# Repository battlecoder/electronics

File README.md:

# electronics
Small Hardware projects that you will most likely find described in my blog: blog.damnsoft.org

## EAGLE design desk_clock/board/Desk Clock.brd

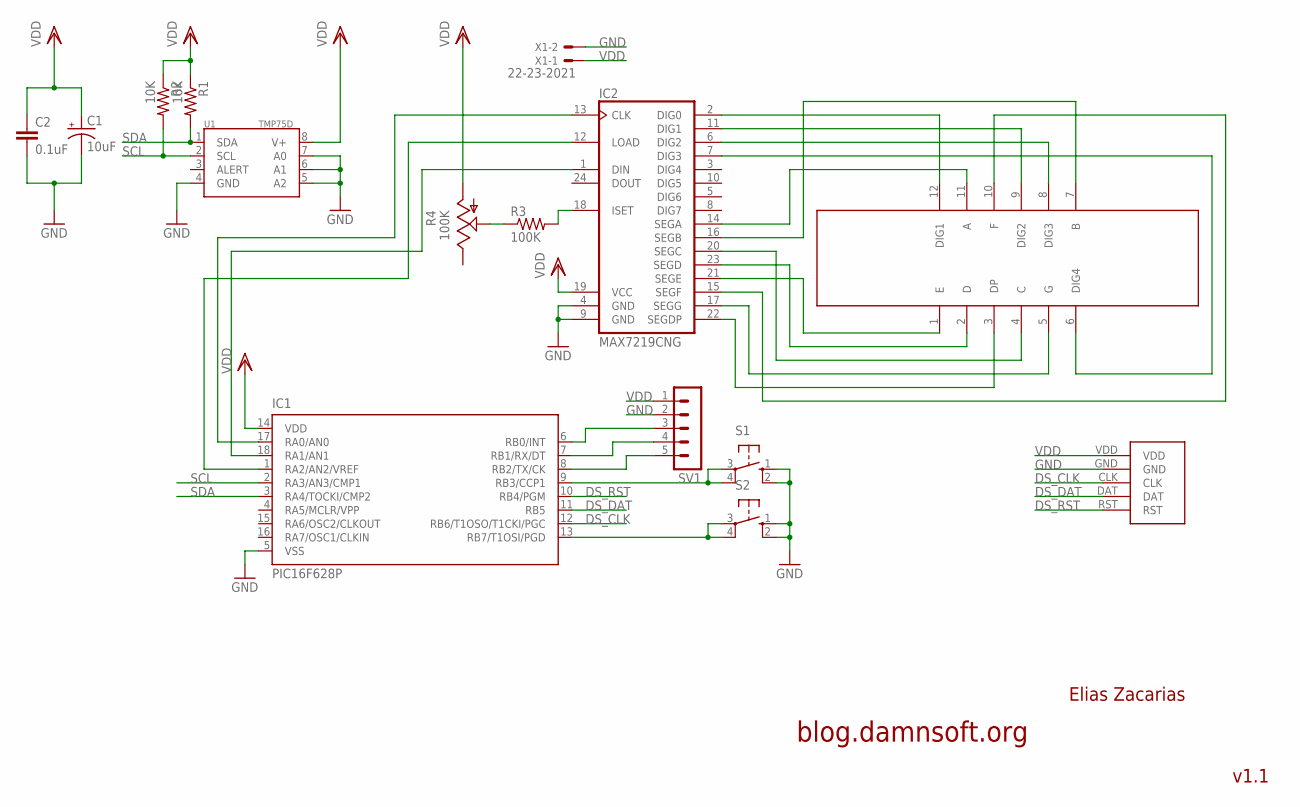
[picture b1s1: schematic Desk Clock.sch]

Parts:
C1: 10uF; E2-4
C2: 0.1uF; C025-025X050
IC1: PIC16F628P; DIL18
IC2: MAX7219CNG; DIL24-3
R1, R2: 10K; 0207/10
R3: 100K; 0207/10
R4: 100K; CA6V
S1, S2: 10-XX; B3F-10XX
SV1: MA05-1
U1: TMP75D; SO-08
U$1: NFD-5642BX; DISPLAY
U$2: DS1302_BOARD
X1: 22-23-2021

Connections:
DS_CLK: IC1.12 (RB6/T1OSO/T1CKI/PGC), U$2.CLK
DS_DAT: IC1.11 (RB5), U$2.DAT
DS_RST: IC1.10 (RB4/PGM), U$2.RST
GND: C1.-, C2.2, IC1.5 (VSS), IC2.4 (GND), IC2.9 (GND), S1.1 (S), S1.2 (S1), S2.1 (S), S2.2 (S1), SV1.2, U1.4 (GND), U1.5 (A2), U1.6 (A1), U1.7 (A0), U$2.GND, X1.2
unnamed: IC2.2 (DIG0), U$1.12 (DIG1)
unnamed: IC2.11 (DIG1), U$1.9 (DIG2)
unnamed: IC2.6 (DIG2), U$1.8 (DIG3)
unnamed: IC2.22 (SEGDP), U$1.3 (DP)
unnamed: IC2.17 (SEGG), U$1.5 (G)
unnamed: IC2.7 (DIG3), U$1.6 (DIG4)
unnamed: IC2.14 (SEGA), U$1.11 (A)
unnamed: IC2.15 (SEGF), U$1.10 (F)
unnamed: IC1.9 (RB3/CCP1), S1.3, S1.4 (P1)
unnamed: IC2.16 (SEGB), U$1.7 (B)
unnamed: IC2.20 (SEGC), U$1.4 (C)
unnamed: IC2.23 (SEGD), U$1.2 (D)
unnamed: IC2.21 (SEGE), U$1.1 (E)
unnamed: IC2.18 (ISET), R3.2
unnamed: R3.1, R4.S
unnamed: IC1.8 (RB2/TX/CK), SV1.5
unnamed: IC1.7 (RB1/RX/DT), SV1.4
unnamed: IC1.6 (RB0/INT), SV1.3
unnamed: IC1.17 (RA0/AN0), IC2.13 (CLK)
unnamed: IC1.13 (RB7/T1OSI/PGD), S2.3, S2.4 (P1)
unnamed: IC1.18 (RA1/AN1), IC2.1 (DIN)
unnamed: IC1.1 (RA2/AN2/VREF), IC2.12 (LOAD)
SCL: IC1.2 (RA3/AN3/CMP1), R2.2, U1.2 (SCL)
SDA: IC1.3 (RA4/TOCKI/CMP2), R1.2, U1.1 (SDA)
VDD: C1.+, C2.1, IC1.14 (VDD), IC2.19 (VCC), R1.1, R2.1, R4.A, SV1.1, U1.8 (V+), U$2.VDD, X1.1

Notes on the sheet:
Elias Zacarias
blog.damnsoft.org
v1.1

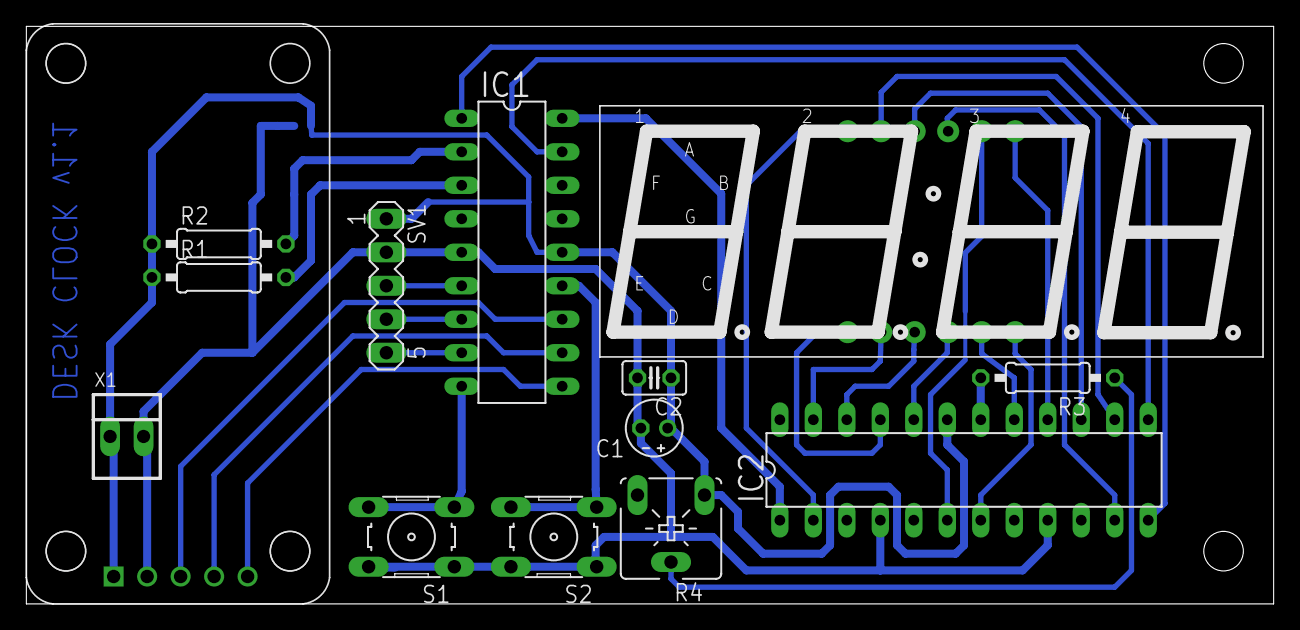
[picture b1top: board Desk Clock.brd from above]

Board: 2 copper layers, 94.6 x 43.8 mm, 15 parts (1 on the bottom side), 29 nets.

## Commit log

2016-06-09 Year is no longer displayed. Date is displayed in a more friendly and descriptive way. The 7SEG char map changed to allow this. Some additional macros were created to help reduce repetition in the co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
2016-06-09 Converted tabs to spaces for consistency across text editors
2016-06-16 Fixed the code that wasn't restoring the write protect flag of the DS1302 after setting time and date, which made the clock vunerable to random halts due to noise, apparently. Also time is queried ev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
2016-07-03 HW revision 1.1. Added a 0.1uF capacitor to improve electric stability and reduce drifting. Also removed version number from the pcb filenames (it's embedded in the schematic and pcb layout now). Fir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
2017-06-25 Hw revision 2.0 (compact board). Firmware updated to reflect that. Several small modifications made for better behavior.
2017-06-27 Added UV Box project
2017-06-27 Added front panel layout (SVG)
2017-06-27 Added overlay SVG file
2017-07-07 Added an alternative full front panel
2018-05-20 Added ESP8266 Programming board
2020-09-14 Improved button handling
    Better / more reliable button detection. Changed mapping of A4 to D0.
